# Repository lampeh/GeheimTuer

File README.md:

# GeheimTuer
Simple sliding door control at Attraktor Makerspace

User Interface:

Prototype 1:

Prototype 2:

Prototype 3, now with laser case and cooling fan:

Spaghetti Schematics. Just a reminder to myself:

Case (created with [Tabbed Box Maker](https://github.com/paulh-rnd/TabbedBoxMaker)):

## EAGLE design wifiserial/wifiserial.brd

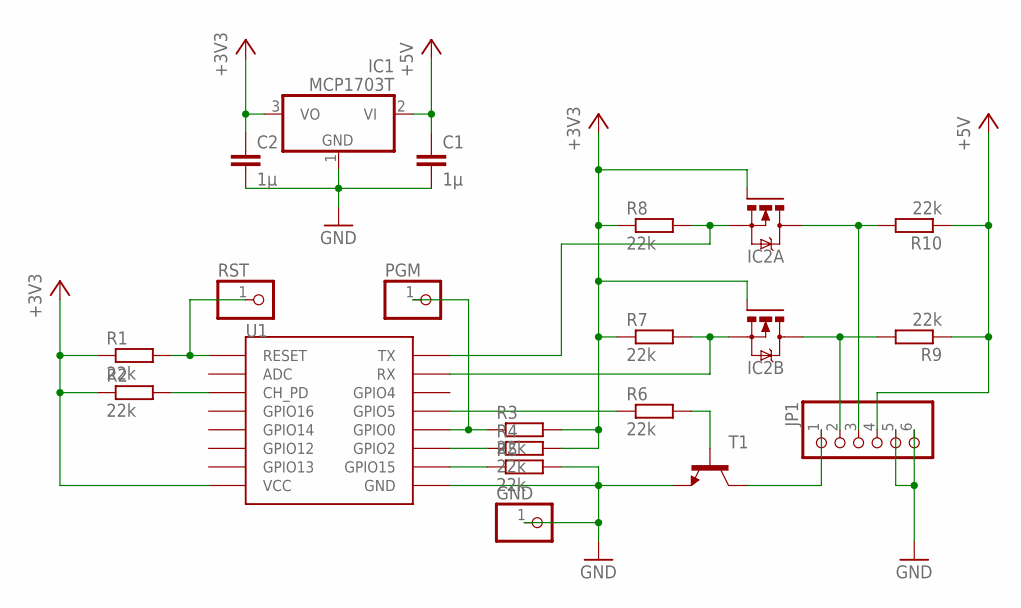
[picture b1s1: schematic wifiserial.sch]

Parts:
C1, C2: 1µ; C0805K
GND: PINHD-1X1; 1X01
IC1: MCP1703T; SOT-89
IC2: NFET2-SSOT6; SSOT-6
JP1: PINHD-1X6; 1X06
PGM: PINHD-1X1; 1X01
R1, R2, R3, R4, R5, R6, R7, R8, R9, R10: 22k; R0805
RST: PINHD-1X1; 1X01
T1: -NPN-SOT23-EBC; SOT23-EBC
U1: ESP12SMD; ESP12-SMD

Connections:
+3V3: C2.1, IC1.3 (VO), IC2.1 (G), IC2.3 (G), R1.1, R2.1, R3.2, R4.2, R7.1, R8.1, U1.VCC
+5V: C1.1, IC1.2 (VI), JP1.4, R9.1, R10.1
GND: C1.2, C2.2, GND.1, IC1.1 (GND), JP1.5, JP1.6, R5.2, T1.E, U1.GND
unnamed: PGM.1, R3.1, U1.GPIO0
unnamed: R4.1, U1.GPIO2
unnamed: R5.1, U1.GPIO15
unnamed: R2.2, U1.CH_PD
unnamed: R1.2, RST.1, U1.RESET
unnamed: R6.1, U1.GPIO5
unnamed: R6.2, T1.B
unnamed: IC2.4 (D), JP1.2, R9.2
unnamed: IC2.6 (D), JP1.3, R10.2
unnamed: JP1.1, T1.C
unnamed: IC2.5 (S), R8.2, U1.TXD0 (TX)
unnamed: IC2.2 (S), R7.2, U1.RXD0 (RX)

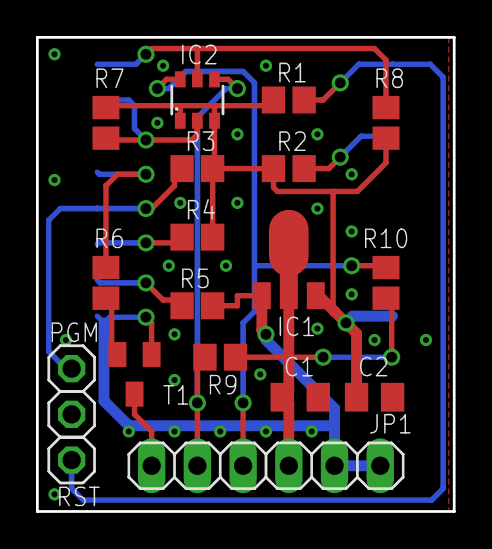
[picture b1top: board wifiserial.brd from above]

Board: 2 copper layers, 23.2 x 26.3 mm, 20 parts (1 on the bottom side), 15 nets.

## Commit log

2016-06-12 Typical Arduino Krumpelcode. Passes all tests, though.
2016-06-13 - renamed sketch for IDE compatibility - updated comments
2016-06-13 - renamed sketch for IDE compatibility
2016-06-14 - quick linear accel works better than slow exponential increase - remote-control debugging - output currentMillis over Serial - changed line endings to \r\n
2016-06-14 added serial debug command to disable driver
2016-06-14 'n' != '\n'. d'Oh!
2016-06-14 use external uint8_t *buffer or **bufptr https://github.com/cpldcpu/light_ws2812
2016-06-14 The MIT License
2016-06-14 use debug() for most debug outputs - some cleanup, too
2016-06-14 check driver condition before switches
2016-06-14 extract pre-increment. same code, anyway
2016-06-14 another small profile adjustment - brake earlier for smooth ending
2016-06-16 - added another set of deglitching variables, so swTrigger can safely be re-armed - probably only useful for swTrigger, not required otherwise
2016-06-17 - blink green when open - another tiny accel adjustment
2016-06-17 cosmetics: use debug(), free motor before Serial.print, typo
2016-06-17 UI experiment: vary ledMoveInterval with drivePWM
2016-06-17 removed sample video from git repo
2016-06-17 branch on short enum motorDir instead of int dir
2016-06-18 - moved config to top (except accel profile) - defined statusLED - debug & cleanup
2016-06-18 experiment: PIR sensor to keep the door open needs more testing
2016-06-18 moved acceleration profile to config block
2016-06-18 readability changes
2016-06-19 - start ledBlink in the on-state - PIR debug
2016-06-19 - display correct mode colors on startup
2016-06-19 frickeltest: start driving on next loop(), don't wait for first stepMillis
2016-06-19 - initialize WS2812 before Serial - set LEDs to blue on setup error
2016-06-20 Logic Analyzer confirms: PWM freq is ~31kHz
2016-06-20 User Manual
2016-06-21 pre-adjustment. belt connector needs work
2016-06-24 AutoFormat wins.
2016-06-24 inhibit automatic close on restart
2016-06-24 cleanup. changed accelProfileIdx to uint8_t
2016-06-25 old & new
2016-06-27 laser-cut case & cooling fan
2016-06-27 Spaghetti Schematics. Just a reminder to myself.
2016-06-27 .png, not .jpg
2016-06-27 laser-cut case
2016-06-27 resized page to drawing
2016-06-27 created with https://github.com/paulh-rnd/TabbedBoxMaker
2016-06-29 experimental: DS18B20 temperature sensors on-board - inefficent code - DS18B20 are too slow - really need a PTC or NTC as planned
2016-07-02 print sensor debug output only on change
2016-07-05 update package: - set watchdog timeout - another profile adjustment, removed slow-start - uint8_t -> byte - fanOverride for remote control - increased minimum sensor difference to 2 - TODO: use class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
2016-07-05 - indentation fixed
2016-07-06 fan motor diode
2016-08-21 3D-printed brackets for LED cover - 3mm notch for translucent acrylic cover - G-Code for Attraktor 3D printer included
2016-08-21 missing fillet in STL export
2016-10-02 - Disable WDT. doesn't work well with Arduino bootloader. Think again
2016-10-02 - another final update to accel profile
2016-10-02 - changed temperature limits
2016-10-02 - quick hack: blink outer LEDs if someone approaches the door
2016-10-02 - fan full/min debug output
2016-10-02 - focus group test: ignore double-clicks on the buttons when opening
2016-10-02 - reshuffled the motor bits. no change in function
2017-04-14 updated work in progress
2017-04-14 ESP-12 board connected to Arduino serial
2017-04-14 visible layers
2017-04-15 moved to subdirs
2017-04-15 minor cleanup, still in progress
2017-04-23 Arduino IDE really wants the directory to be named GeheimTuer
